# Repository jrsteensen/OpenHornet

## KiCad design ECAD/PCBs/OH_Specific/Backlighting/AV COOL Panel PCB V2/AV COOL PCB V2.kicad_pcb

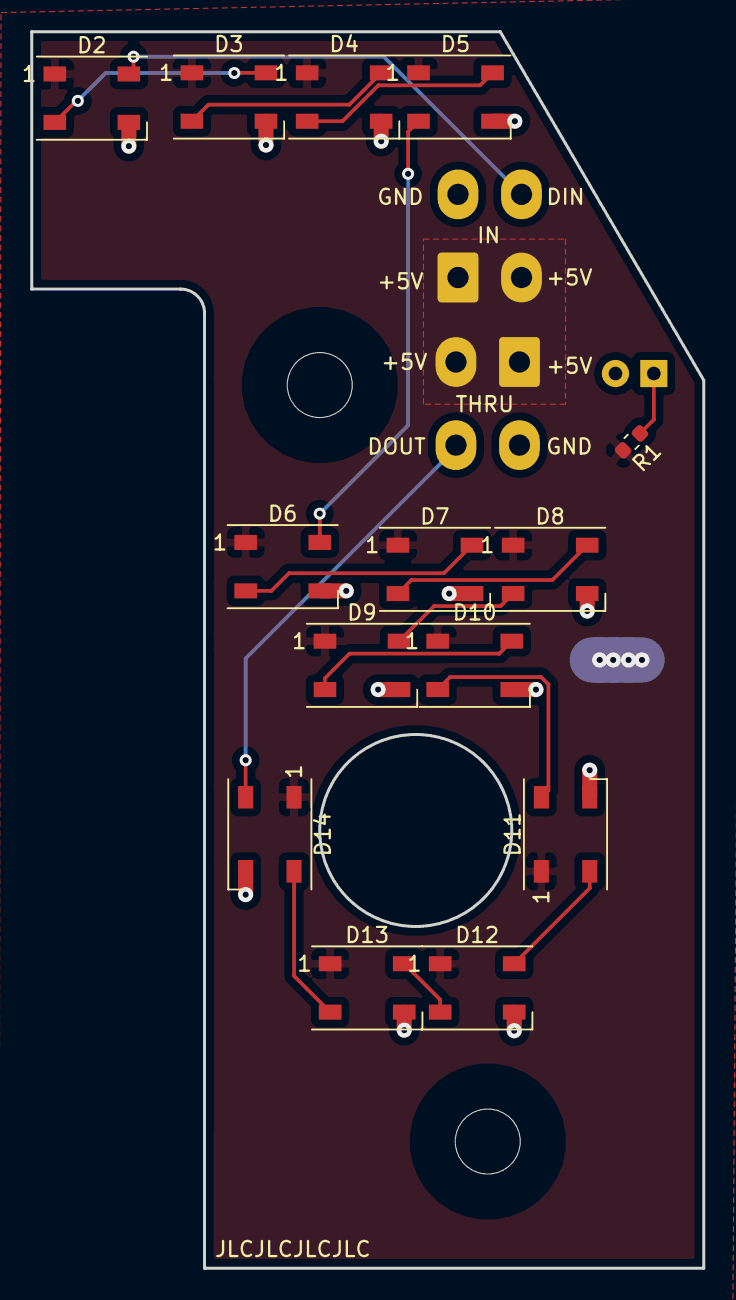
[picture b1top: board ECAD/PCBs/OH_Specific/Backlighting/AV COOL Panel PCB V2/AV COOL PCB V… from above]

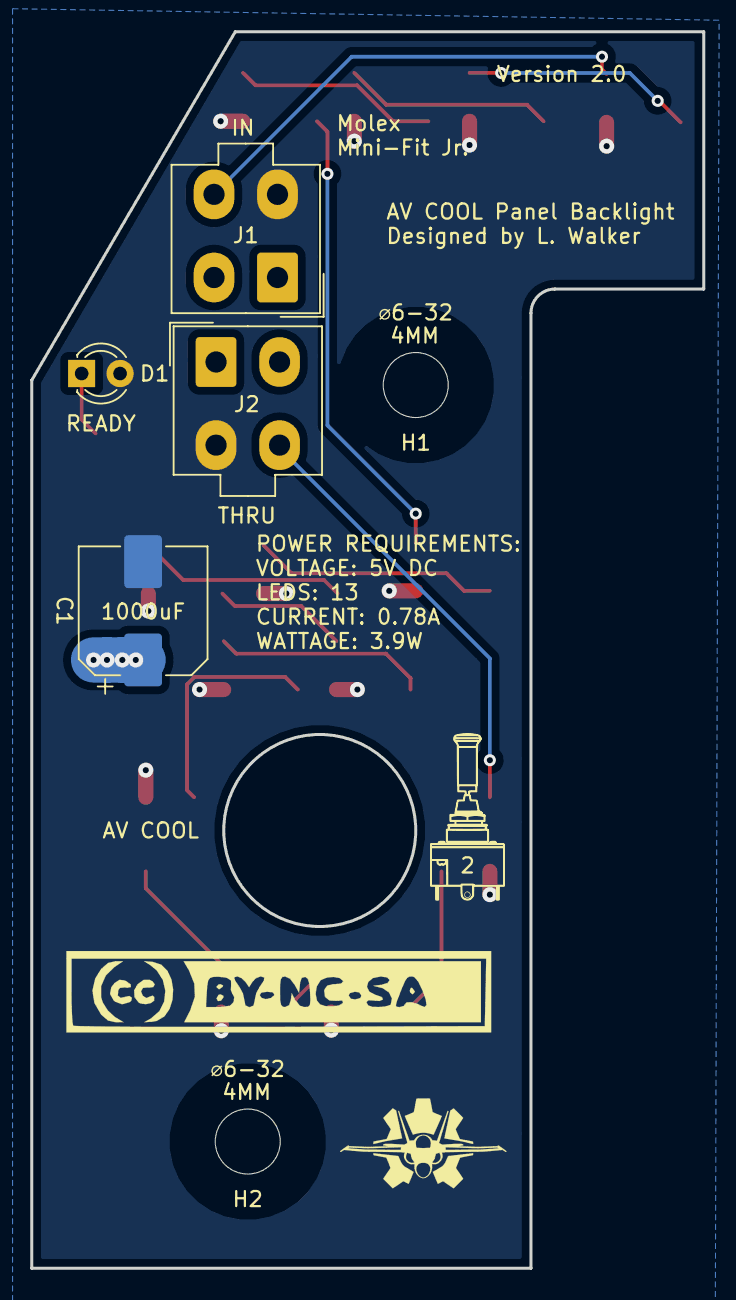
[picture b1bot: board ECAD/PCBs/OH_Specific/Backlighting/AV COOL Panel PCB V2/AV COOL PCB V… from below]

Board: 2 copper layers, 44.5 x 81.8 mm, 18 parts (4 on the bottom side), 17 nets.

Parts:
C1: C_Polarized; CP_Elec_8x10
D1: LED; LED_D3.0mm
D2, D3, D4, D5, D6, D7, D8, D9, D10, D11, D12, D13, D14: WS2812B; LED_WS2812B_PLCC4_5.0x5.0mm_P3.2mm
J1, J2: Conn_01x04_Female; Molex_Mini-Fit_Jr_5566-04A_2x02_P4.20mm_Vertical
R1: R; R_0603_1608Metric

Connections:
/DATAIN: D2.4, J1.4
/DATAOUT: D14.2, J2.4
/LED+5V: C1.1, D2.1, D3.1, D4.1, D5.1, D6.1, D7.1, D8.1, D9.1, D10.1, D11.1, D12.1, D13.1, D14.1, J1.1, J1.2, J2.1, J2.2, R1.2
/LEDGND: C1.2, D1.2, D2.3, D3.3, D4.3, D5.3, D6.3, D7.3, D8.3, D9.3, D10.3, D11.3, D12.3, D13.3, D14.3, J1.3, J2.3
unnamed: D1.1, R1.1
unnamed: D2.2, D3.4
unnamed: D3.2, D4.4
unnamed: D4.2, D5.4
unnamed: D5.2, D6.4
unnamed: D6.2, D7.4
unnamed: D7.2, D8.4
unnamed: D8.2, D9.4
unnamed: D10.2, D11.4
unnamed: D9.2, D10.4
unnamed: D11.2, D12.4
unnamed: D12.2, D13.4
unnamed: D13.2, D14.4

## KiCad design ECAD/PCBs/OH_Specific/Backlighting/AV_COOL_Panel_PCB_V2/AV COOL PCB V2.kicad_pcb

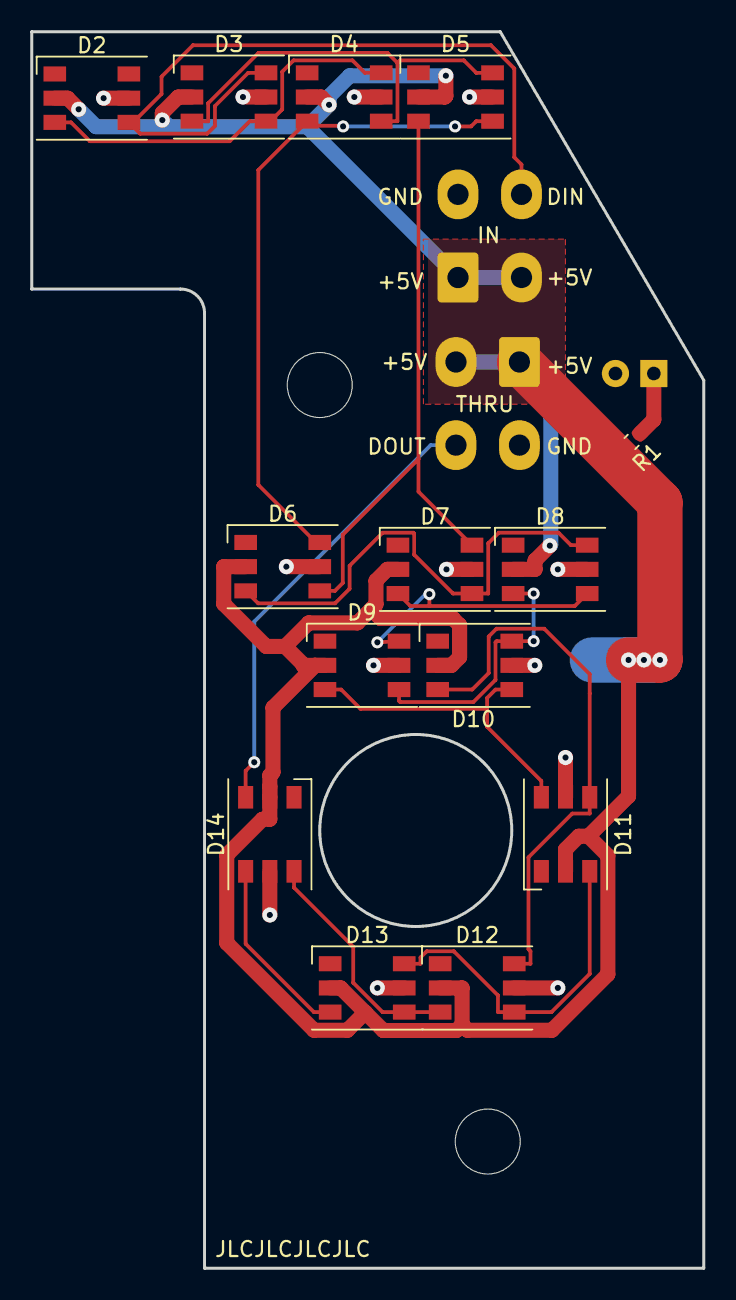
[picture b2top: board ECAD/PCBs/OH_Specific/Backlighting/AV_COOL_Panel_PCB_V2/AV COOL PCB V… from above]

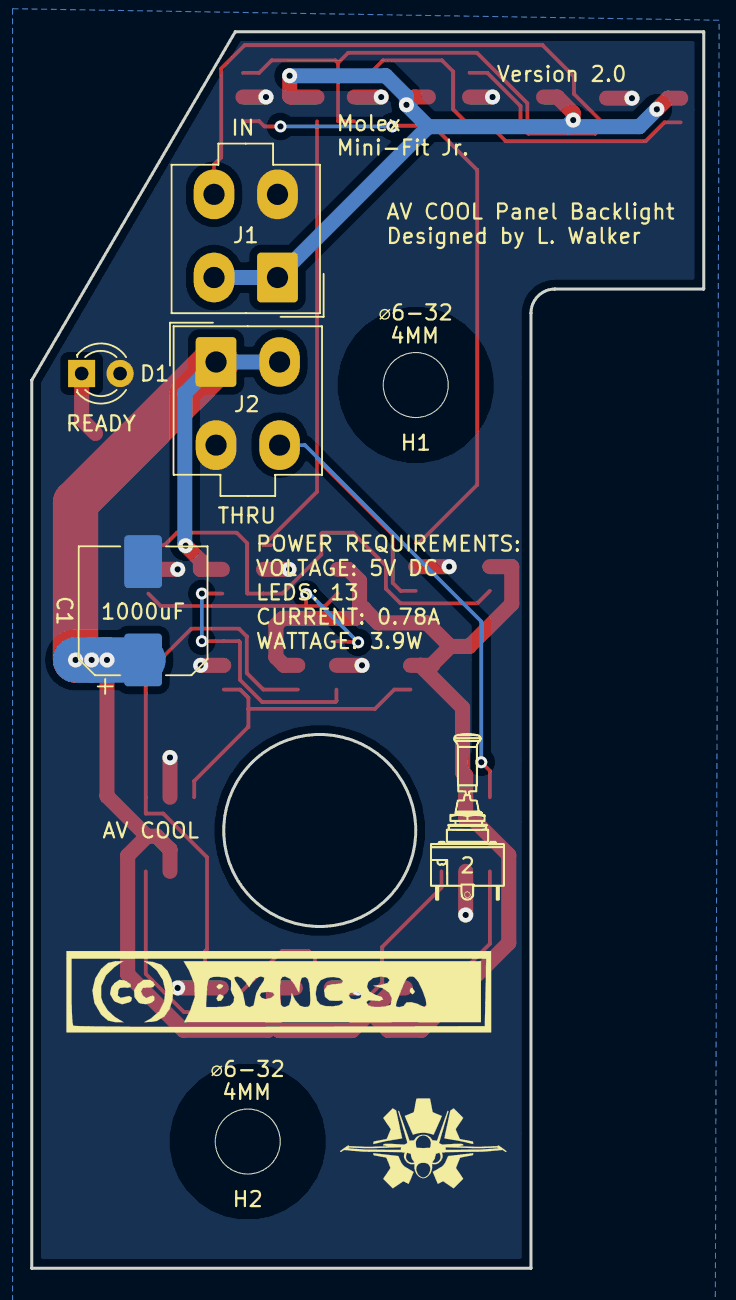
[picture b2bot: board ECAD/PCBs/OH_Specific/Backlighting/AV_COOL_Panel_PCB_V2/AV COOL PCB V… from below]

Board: 2 copper layers, 44.5 x 81.8 mm, 18 parts (4 on the bottom side), 17 nets.

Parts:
C1: C_Polarized; CP_Elec_8x10
D1: LED; LED_D3.0mm
D2, D3, D4, D5, D6, D7, D8, D9, D10, D11, D12, D13, D14: WS2813; LED_WS2812_PLCC6_5.0x5.0mm_P1.6mm
J1, J2: Conn_01x04_Female; Molex_Mini-Fit_Jr_5566-04A_2x02_P4.20mm_Vertical
R1: R; R_0603_1608Metric

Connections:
/DATAIN: D2.4, D3.6, J1.4
/DATAOUT: D14.3, J2.4
/LED+5V: C1.1, D2.2, D3.2, D4.2, D5.2, D6.2, D7.2, D8.2, D9.2, D10.2, D11.2, D12.2, D13.2, D14.2, J1.1, J1.2, J2.1, J2.2, R1.2
/LEDGND: C1.2, D1.2, D2.5, D3.5, D4.5, D5.5, D6.5, D7.5, D8.5, D9.5, D10.5, D11.5, D12.5, D13.5, D14.5, J1.3, J2.3
unnamed: D1.1, R1.1
unnamed: D2.3, D3.4, D4.6
unnamed: D3.3, D4.4, D5.6
unnamed: D4.3, D5.4, D6.6
unnamed: D5.3, D6.4, D7.6
unnamed: D6.3, D7.4, D8.6
unnamed: D7.3, D8.4, D9.6
unnamed: D10.3, D11.4, D12.6
unnamed: D9.3, D10.4, D11.6
unnamed: D8.3, D9.4, D10.6
unnamed: D11.3, D12.4, D13.6
unnamed: D12.3, D13.4, D14.6
unnamed: D13.3, D14.4

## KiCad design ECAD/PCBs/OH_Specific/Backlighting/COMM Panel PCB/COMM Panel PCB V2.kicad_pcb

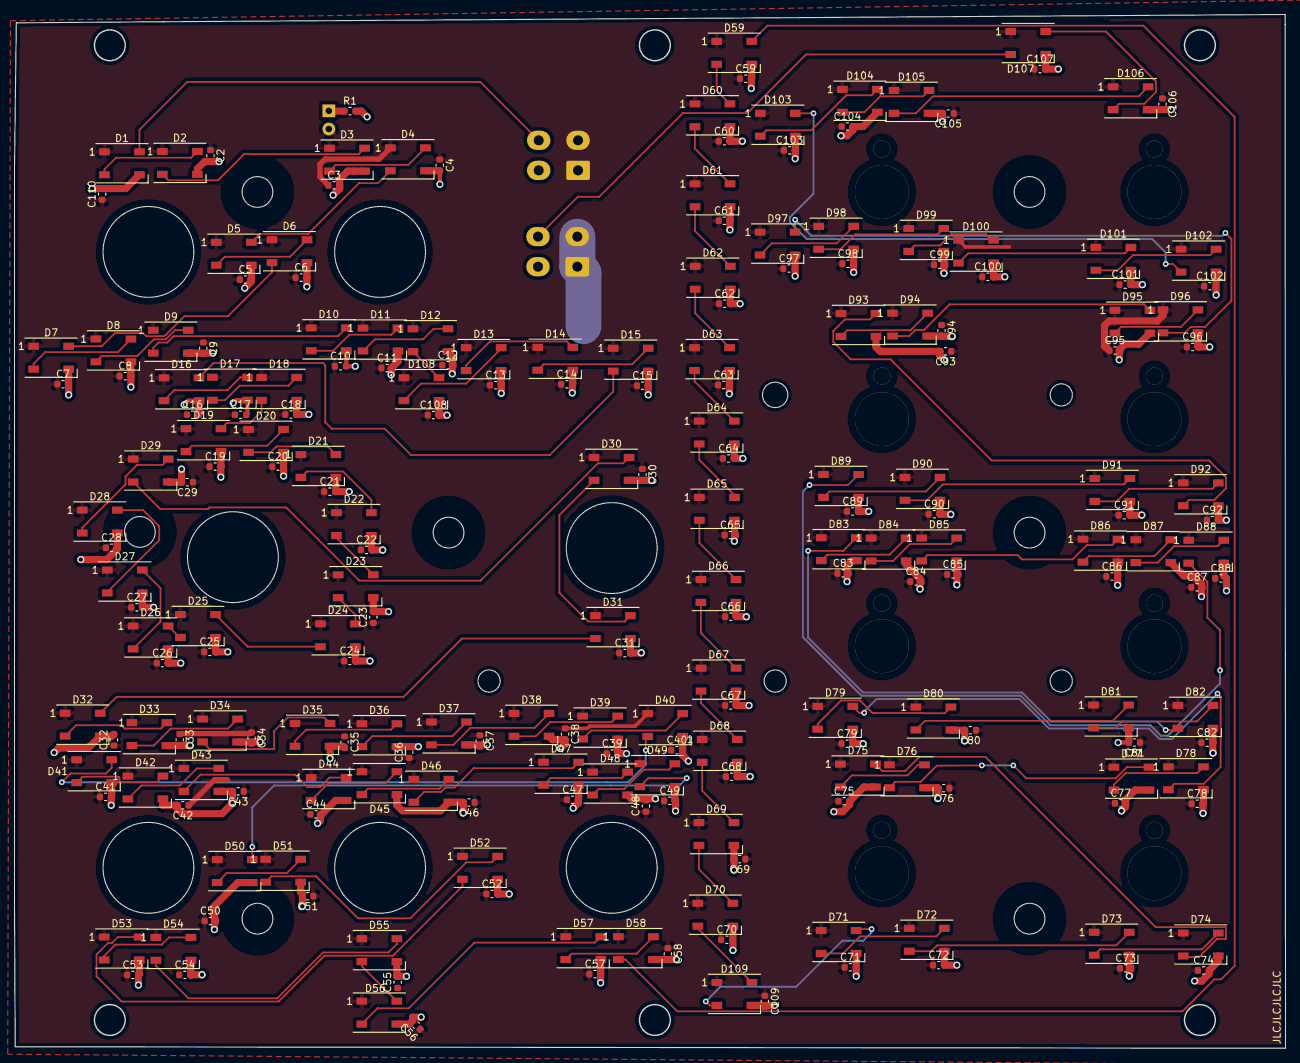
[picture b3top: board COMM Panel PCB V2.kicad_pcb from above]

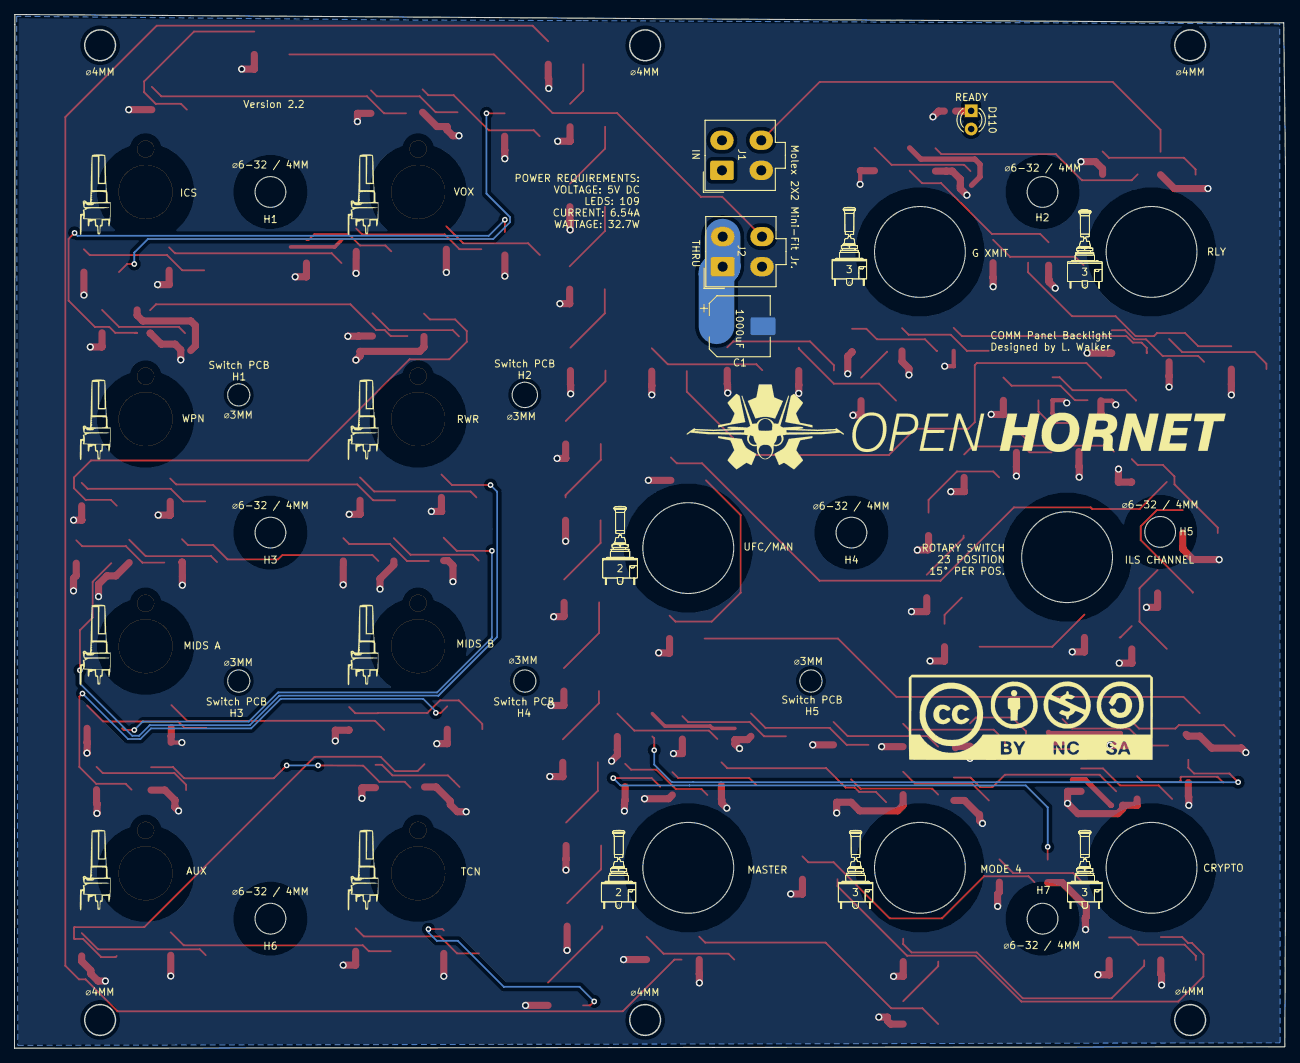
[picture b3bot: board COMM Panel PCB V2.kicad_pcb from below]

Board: 2 copper layers, 177.7 x 144.5 mm, 258 parts (19 on the bottom side), 113 nets.

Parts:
1, 2, 4, 5, 6, 7: SxAL_Toggle_13x13mm
8, 9, 10, 11, 12, 13, 14, 16: BR10K_Pot_11mm_x_11mm
17, 19, 20, 21, 22, 23, 24: OH_Panel_Fastner_Keepout; OH_Panel_6-32_PHS
C1: C_Polarized; CP_Elec_8x10
C2, C3, C4, C5, C6, C7, C8, C9, C10, C11, C12, C13, C14, C15, C16, C17, C18, C19, C20, C21, C22, C23, C24, C25, C26, C27, C28, C29, C30, C31, C32, C33, C34, C35, C36, C37, C38, C39, C40, C41, C42, C43, C44, C46, C47, C48, C49, C50, C51, C52, C53, C54, C55, C56, C57, C58, C59, C60, C61, C62, C63, C64, C65, C66, C67, C68, C69, C70, C71, C72, C73, C74, C75, C76, C77, C78, C79, C80, C81, C82, C83, C84, C85, C86, C87, C88, C89, C90, C91, C92, C93, C94, C95, C96, C97, C98, C99, C100, C101, C102, C103, C104, C105, C106, C107, C108, C109, C110: C; C_0603_1608Metric
D1, D2, D3, D4, D5, D6, D7, D8, D9, D10, D11, D12, D13, D14, D15, D16, D17, D18, D19, D20, D21, D22, D23, D24, D25, D26, D27, D28, D29, D30, D31, D32, D33, D34, D35, D36, D37, D38, D39, D40, D41, D42, D43, D44, D45, D46, D47, D48, D49, D50, D51, D52, D53, D54, D55, D56, D57, D58, D59, D60, D61, D62, D63, D64, D65, D66, D67, D68, D69, D70, D71, D72, D73, D74, D75, D76, D77, D78, D79, D80, D81, D82, D83, D84, D85, D86, D87, D88, D89, D90, D91, D92, D93, D94, D95, D96, D97, D98, D99, D100, D101, D102, D103, D104, D105, D106, D107, D108, D109: WS2812B; LED_WS2812B_PLCC4_5.0x5.0mm_P3.2mm
D110: LED; LED_D3.0mm
G1, G2, G5, G6: LOGO; S3ALToggle
G3: SxAL_Toggle_13x13mm
G4, G7: LOGO; S2ALToggle
G8, G9, G10, G11, G12, G13, G14, G15: LOGO; BR10KPot
J1, J2: Conn_01x04_Female; Molex_Mini-Fit_Jr_5566-04A_2x02_P4.20mm_Vertical
R1: R; R_0603_1608Metric

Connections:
/DATAIN: D1.4, J1.4
/DATAOUT: D107.2, J2.4
/LED+5V: C1.1, C2.1, C3.1, C4.1, C5.1, C6.1, C7.1, C8.1, C9.1, C10.1, C11.1, C12.1, C13.1, C14.1, C15.1, C16.1, C17.1, C18.1, C19.1, C20.1, C21.1, C22.1, C23.1, C24.1, C25.1, C26.1, C27.1, C28.1, C29.1, C30.1, C31.1, C32.1, C33.1, C34.1, C35.1, C36.1, C37.1, C38.1, C39.1, C40.1, C41.1, C42.1, C43.1, C44.1, C46.1, C47.1, C48.1, C49.1, C50.1, C51.1, C52.1, C53.1, C54.1, C55.1, C56.1, C57.1, C58.1, C59.1, C60.1, C61.1, C62.1, C63.1, C64.1, C65.1, C66.1, C67.1, C68.1, C69.1, C70.1, C71.1, C72.1, C73.1, C74.1, C75.1, C76.1, C77.1, C78.1, C79.1, C80.1, C81.1, C82.1, C83.1, C84.1, C85.1, C86.1, C87.1, C88.1, C89.1, C90.1, C91.1, C92.1, C93.1, C94.1, C95.1, C96.1, C97.1, C98.1, C99.1, C100.1, C101.1, C102.1, C103.1, C104.1, C105.1, C106.1, C107.1, C108.1, C109.1, C110.1, D1.1, D2.1, D3.1, D4.1, D5.1, D6.1, D7.1, D8.1, D9.1, D10.1, D11.1, D12.1, D13.1, D14.1, D15.1, D16.1, D17.1, D18.1, D19.1, D20.1, D21.1, D22.1, D23.1, D24.1, D25.1, D26.1, D27.1, D28.1, D29.1, D30.1, D31.1, D32.1, D33.1, D34.1, D35.1, D36.1, D37.1, D38.1, D39.1, D40.1, D41.1, D42.1, D43.1, D44.1, D45.1, D46.1, D47.1, D48.1, D49.1, D50.1, D51.1, D52.1, D53.1, D54.1, D55.1, D56.1, D57.1, D58.1, D59.1, D60.1, D61.1, D62.1, D63.1, D64.1, D65.1, D66.1, D67.1, D68.1, D69.1, D70.1, D71.1, D72.1, D73.1, D74.1, D75.1, D76.1, D77.1, D78.1, D79.1, D80.1, D81.1, D82.1, D83.1, D84.1, D85.1, D86.1, D87.1, D88.1, D89.1, D90.1, D91.1, D92.1, D93.1, D94.1, D95.1, D96.1, D97.1, D98.1, D99.1, D100.1, D101.1, D102.1, D103.1, D104.1, D105.1, D106.1, D107.1, D108.1, D109.1, D110.2, J1.1, J1.2, J2.1, J2.2
/LEDGND: C1.2, C2.2, C3.2, C4.2, C5.2, C6.2, C7.2, C8.2, C9.2, C10.2, C11.2, C12.2, C13.2, C14.2, C15.2, C16.2, C17.2, C18.2, C19.2, C20.2, C21.2, C22.2, C23.2, C24.2, C25.2, C26.2, C27.2, C28.2, C29.2, C30.2, C31.2, C32.2, C33.2, C34.2, C35.2, C36.2, C37.2, C38.2, C39.2, C40.2, C41.2, C42.2, C43.2, C44.2, C46.2, C47.2, C48.2, C49.2, C50.2, C51.2, C52.2, C53.2, C54.2, C55.2, C56.2, C57.2, C58.2, C59.2, C60.2, C61.2, C62.2, C63.2, C64.2, C65.2, C66.2, C67.2, C68.2, C69.2, C70.2, C71.2, C72.2, C73.2, C74.2, C75.2, C76.2, C77.2, C78.2, C79.2, C80.2, C81.2, C82.2, C83.2, C84.2, C85.2, C86.2, C87.2, C88.2, C89.2, C90.2, C91.2, C92.2, C93.2, C94.2, C95.2, C96.2, C97.2, C98.2, C99.2, C100.2, C101.2, C102.2, C103.2, C104.2, C105.2, C106.2, C107.2, C108.2, C109.2, C110.2, D1.3, D2.3, D3.3, D4.3, D5.3, D6.3, D7.3, D8.3, D9.3, D10.3, D11.3, D12.3, D13.3, D14.3, D15.3, D16.3, D17.3, D18.3, D19.3, D20.3, D21.3, D22.3, D23.3, D24.3, D25.3, D26.3, D27.3, D28.3, D29.3, D30.3, D31.3, D32.3, D33.3, D34.3, D35.3, D36.3, D37.3, D38.3, D39.3, D40.3, D41.3, D42.3, D43.3, D44.3, D45.3, D46.3, D47.3, D48.3, D49.3, D50.3, D51.3, D52.3, D53.3, D54.3, D55.3, D56.3, D57.3, D58.3, D59.3, D60.3, D61.3, D62.3, D63.3, D64.3, D65.3, D66.3, D67.3, D68.3, D69.3, D70.3, D71.3, D72.3, D73.3, D74.3, D75.3, D76.3, D77.3, D78.3, D79.3, D80.3, D81.3, D82.3, D83.3, D84.3, D85.3, D86.3, D87.3, D88.3, D89.3, D90.3, D91.3, D92.3, D93.3, D94.3, D95.3, D96.3, D97.3, D98.3, D99.3, D100.3, D101.3, D102.3, D103.3, D104.3, D105.3, D106.3, D107.3, D108.3, D109.3, J1.3, J2.3, R1.2
unnamed: D1.2, D2.4
unnamed: D2.2, D3.4
unnamed: D3.2, D4.4
unnamed: D4.2, D5.4
unnamed: D5.2, D6.4
unnamed: D6.2, D7.4
unnamed: D7.2, D8.4
unnamed: D8.2, D9.4
unnamed: D10.2, D11.4
unnamed: D9.2, D10.4
unnamed: D11.2, D12.4
unnamed: D13.2, D14.4
unnamed: D14.2, D15.4
unnamed: D15.2, D16.4
unnamed: D16.2, D17.4
unnamed: D17.2, D18.4
unnamed: D18.2, D19.4
unnamed: D19.2, D20.4
unnamed: D20.2, D21.4
unnamed: D21.2, D22.4
unnamed: D22.2, D23.4
unnamed: D23.2, D24.4
unnamed: D24.2, D25.4
unnamed: D25.2, D26.4
unnamed: D26.2, D27.4
unnamed: D27.2, D28.4
unnamed: D28.2, D29.4
unnamed: D29.2, D30.4
unnamed: D30.2, D31.4
unnamed: D31.2, D32.4
unnamed: D32.2, D33.4
unnamed: D33.2, D34.4
unnamed: D34.2, D35.4
unnamed: D35.2, D36.4
unnamed: D36.2, D37.4
unnamed: D37.2, D38.4
unnamed: D38.2, D39.4
unnamed: D39.2, D40.4
unnamed: D40.2, D41.4
unnamed: D41.2, D42.4
unnamed: D42.2, D43.4
unnamed: D43.2, D44.4
unnamed: D44.2, D45.4
unnamed: D45.2, D46.4
unnamed: D46.2, D47.4
unnamed: D47.2, D48.4
unnamed: D48.2, D49.4
unnamed: D49.2, D50.4
unnamed: D50.2, D51.4
unnamed: D51.2, D52.4
unnamed: D52.2, D53.4
unnamed: D53.2, D54.4
unnamed: D54.2, D55.4
unnamed: D55.2, D56.4
unnamed: D56.2, D57.4
unnamed: D57.2, D58.4
unnamed: D58.2, D59.4
unnamed: D59.2, D60.4
unnamed: D60.2, D61.4
unnamed: D61.2, D62.4
unnamed: D62.2, D63.4
unnamed: D63.2, D64.4
unnamed: D64.2, D65.4
unnamed: D65.2, D66.4
unnamed: D66.2, D67.4
unnamed: D67.2, D68.4
unnamed: D68.2, D69.4
unnamed: D69.2, D70.4
unnamed: D71.2, D72.4
unnamed: D72.2, D73.4
unnamed: D73.2, D74.4
unnamed: D74.2, D75.4
unnamed: D75.2, D76.4
unnamed: D76.2, D77.4
unnamed: D77.2, D78.4
unnamed: D78.2, D79.4
unnamed: D79.2, D80.4
unnamed: D80.2, D81.4
unnamed: D81.2, D82.4
unnamed: D82.2, D83.4
unnamed: D83.2, D84.4
unnamed: D84.2, D85.4
unnamed: D85.2, D86.4
unnamed: D86.2, D87.4
unnamed: D87.2, D88.4
unnamed: D88.2, D89.4
unnamed: D89.2, D90.4
unnamed: D90.2, D91.4
unnamed: D91.2, D92.4
unnamed: D92.2, D93.4
unnamed: D93.2, D94.4
unnamed: D94.2, D95.4
unnamed: D95.2, D96.4
unnamed: D96.2, D97.4
unnamed: D97.2, D98.4
unnamed: D98.2, D99.4
unnamed: D100.2, D101.4
unnamed: D99.2, D100.4
unnamed: D101.2, D102.4
unnamed: D102.2, D103.4
unnamed: D103.2, D104.4
unnamed: D104.2, D105.4
unnamed: D105.2, D106.4
unnamed: D106.2, D107.4
unnamed: D13.4, D108.2
unnamed: D12.2, D108.4
unnamed: D71.4, D109.2
unnamed: D70.2, D109.4
unnamed: D110.1, R1.1
